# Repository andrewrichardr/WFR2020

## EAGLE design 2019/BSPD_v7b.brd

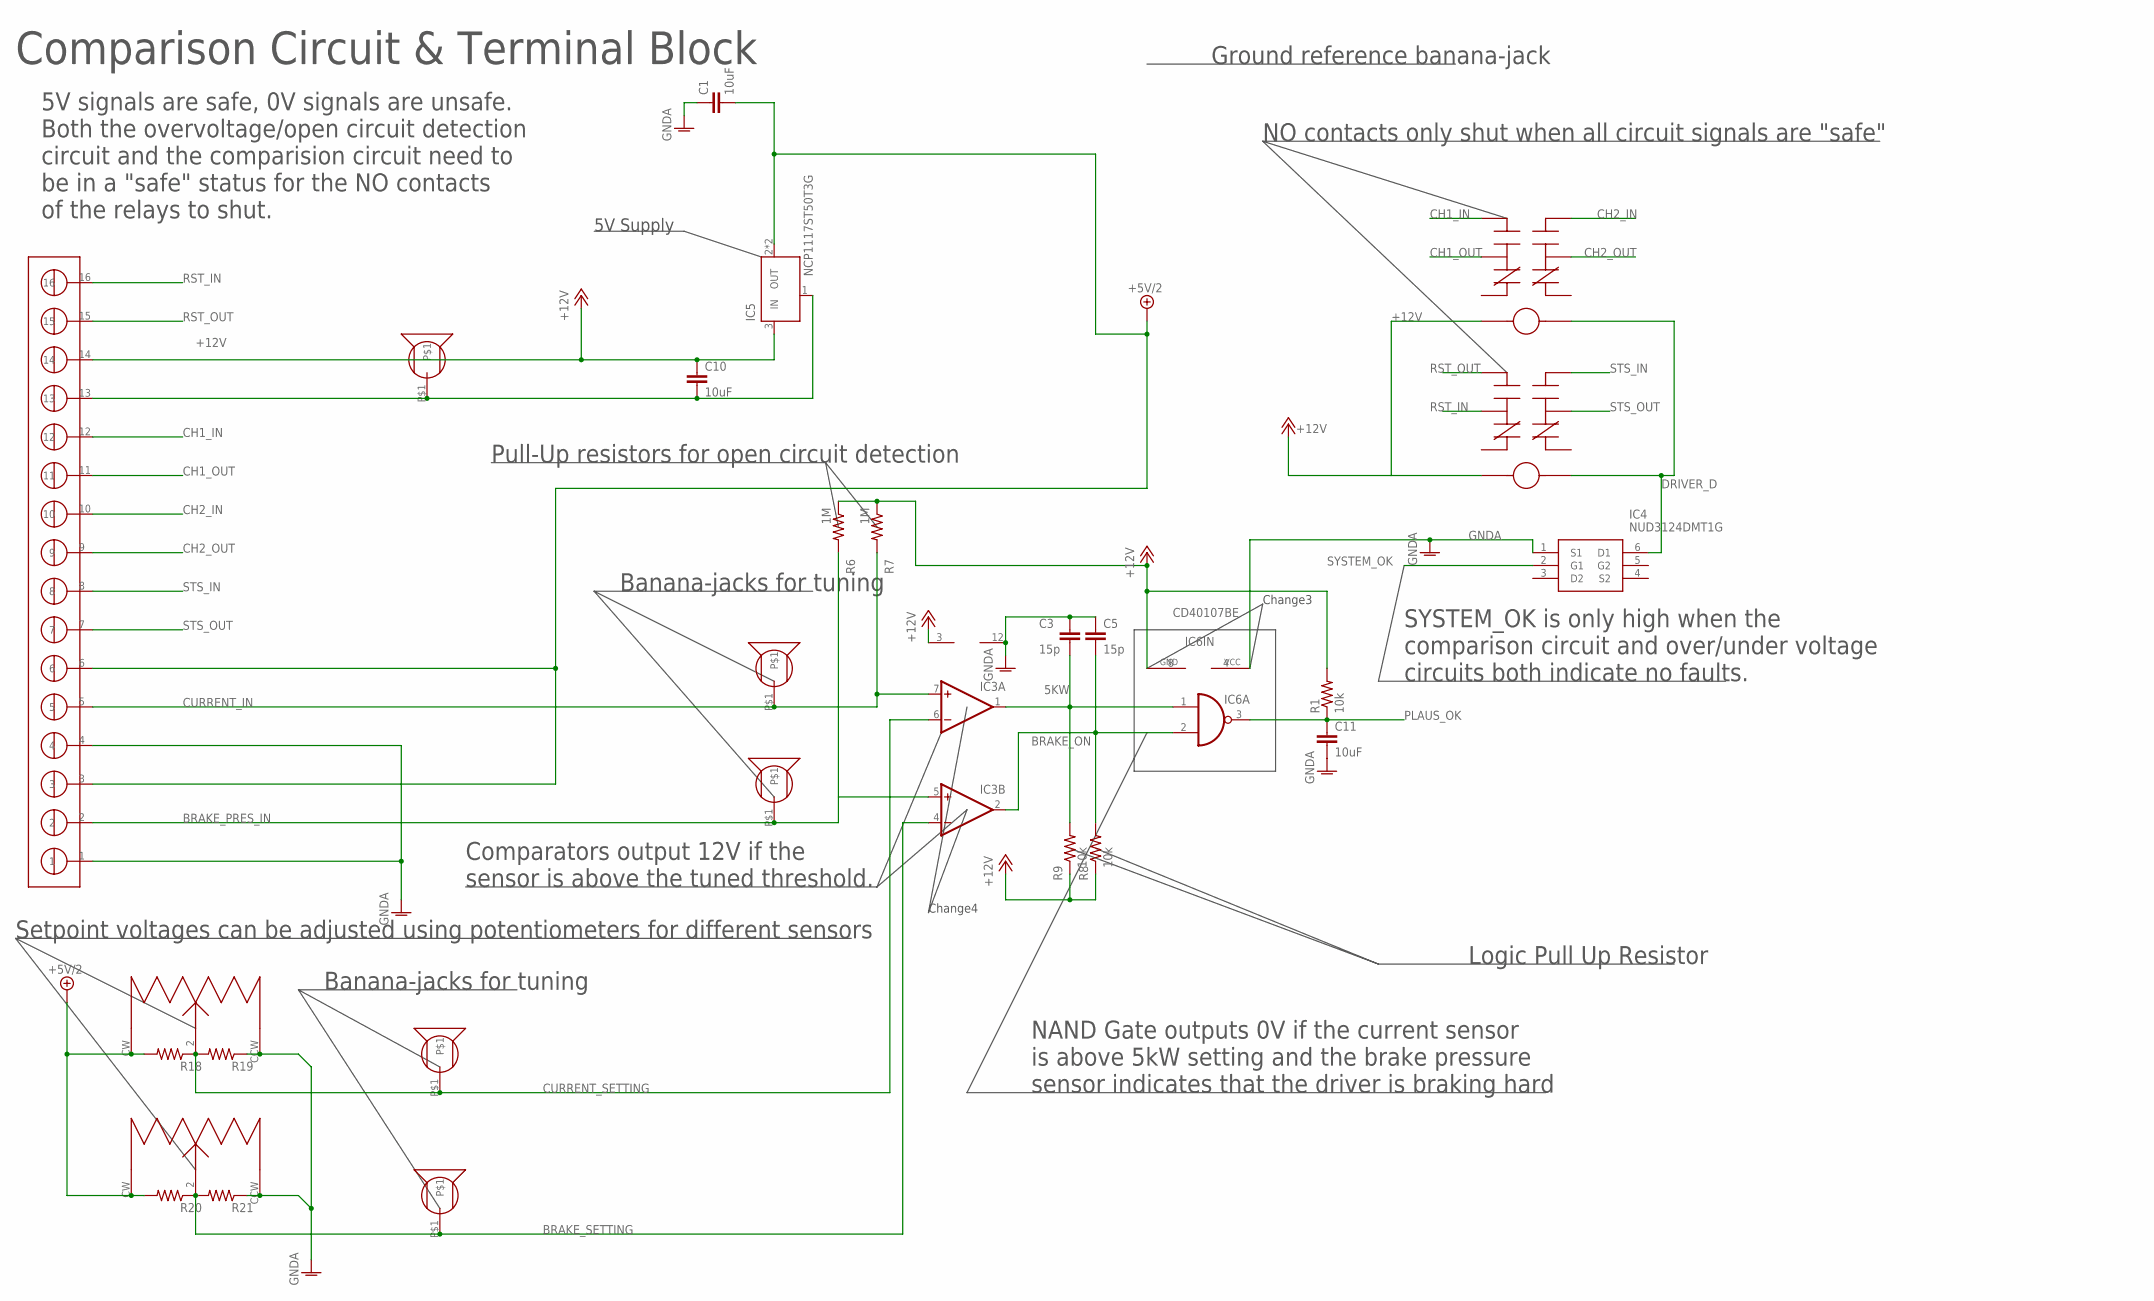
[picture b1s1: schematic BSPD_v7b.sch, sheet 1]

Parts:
C1, C10, C11: 10uF; C0805
C3, C5: 15p; C0805
IC3: 4AMP_P11+7N; DIL14
IC4: NUD3124DMT1G; SOT95P275X110-6N
IC5: NCP1117ST50T3G; SOT223
IC6: CD40107BE; DIL08
R1, R8, R9: 10k; M0805
R6, R7: 1M; M0805
R18, R19, R20, R21: R-US_M0805; M0805
U$1: BSPD_PARTS_AMPH_OQ1632500000G; BSPD_PARTS_3_81MM_16PIN
U$4, U$18, U$19, U$21, U$22: BSPD_PARTS_MP_BANANA_PLUG; BSPD_PARTS_BANANA_PLUG
U$10, U$11: POT_3310Y-025-103L; 3310Y
U$12, U$13: BSPD_PARTS_RLY_V23079A1001B301; BSPD_PARTS_V23079F1101B301

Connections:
5KW: C3.2, IC3.1 (OUT), IC6.1 (I0), R9.2
+5V/2: C1.2, IC5.2 (OUT), IC5.4 (OUT), R18.2, R20.2, U$1.3, U$1.6, U$10.CW, U$11.CW; also elsewhere on the board
+12V: C10.1, IC3.3 (V+), IC5.3 (IN), IC6.8 (GND), R1.2, R6.1, R7.1, R8.1, R9.1, U$1.14, U$12.1, U$13.1; also elsewhere on the board
BRAKE_ON: C5.2, IC3.2 (OUT), IC6.2 (I1), R8.2
BRAKE_PRES_IN: IC3.5 (+IN), R6.2, U$1.2, U$22.P$1; also elsewhere on the board
BRAKE_SETTING: IC3.4 (-IN), R20.1, R21.2, U$10.2 (VO), U$19.P$1
CH1_IN: U$1.12, U$13.5
CH1_OUT: U$1.11, U$13.4
CH2_IN: U$1.10, U$13.8
CH2_OUT: U$1.9, U$13.9
CURRENT_IN: IC3.7 (+IN), R7.2, U$1.5, U$21.P$1; also elsewhere on the board
CURRENT_SETTING: IC3.6 (-IN), R18.1, R19.2, U$11.2 (VO), U$18.P$1
DRIVER_D: IC4.6 (D1), U$12.12, U$13.12
GNDA: C1.1, C3.1, C5.1, C10.2, C11.2, IC3.12 (V-), IC4.1 (S1), IC5.1 (GND), IC6.4 (VCC), R19.1, R21.1, U$1.1, U$1.4, U$1.13, U$4.P$1, U$10.CCW, U$11.CCW; also elsewhere on the board
PLAUS_OK: C11.1, IC6.3 (O), R1.1; also elsewhere on the board
RST_IN: U$1.16, U$12.4
RST_OUT: U$1.15, U$12.5
STS_IN: U$1.8, U$12.8
STS_OUT: U$1.7, U$12.9
SYSTEM_OK: IC4.2 (G1); also elsewhere on the board

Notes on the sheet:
Comparison Circuit & Terminal Block
Logic Pull Up Resistor
Pull-Up resistors for open circuit detection
Banana-jacks for tuning
Setpoint voltages can be adjusted using potentiometers for different sensors
Ground reference banana-jack
5V Supply
NO contacts only shut when all circuit signals are "safe"
5V signals are safe, 0V signals are unsafe. Both the overvoltage/open circuit detection circuit and the comparision circuit need to be in a "safe" status for the NO contacts of the relays to shut.
NAND Gate outputs 0V if the current sensor is above 5kW setting and the brake pressure sensor indicates that the driver is braking hard
Comparators output 12V if the sensor is above the tuned threshold.
SYSTEM_OK is only high when the comparison circuit and over/under voltage circuits both indicate no faults.
Change3
Change4

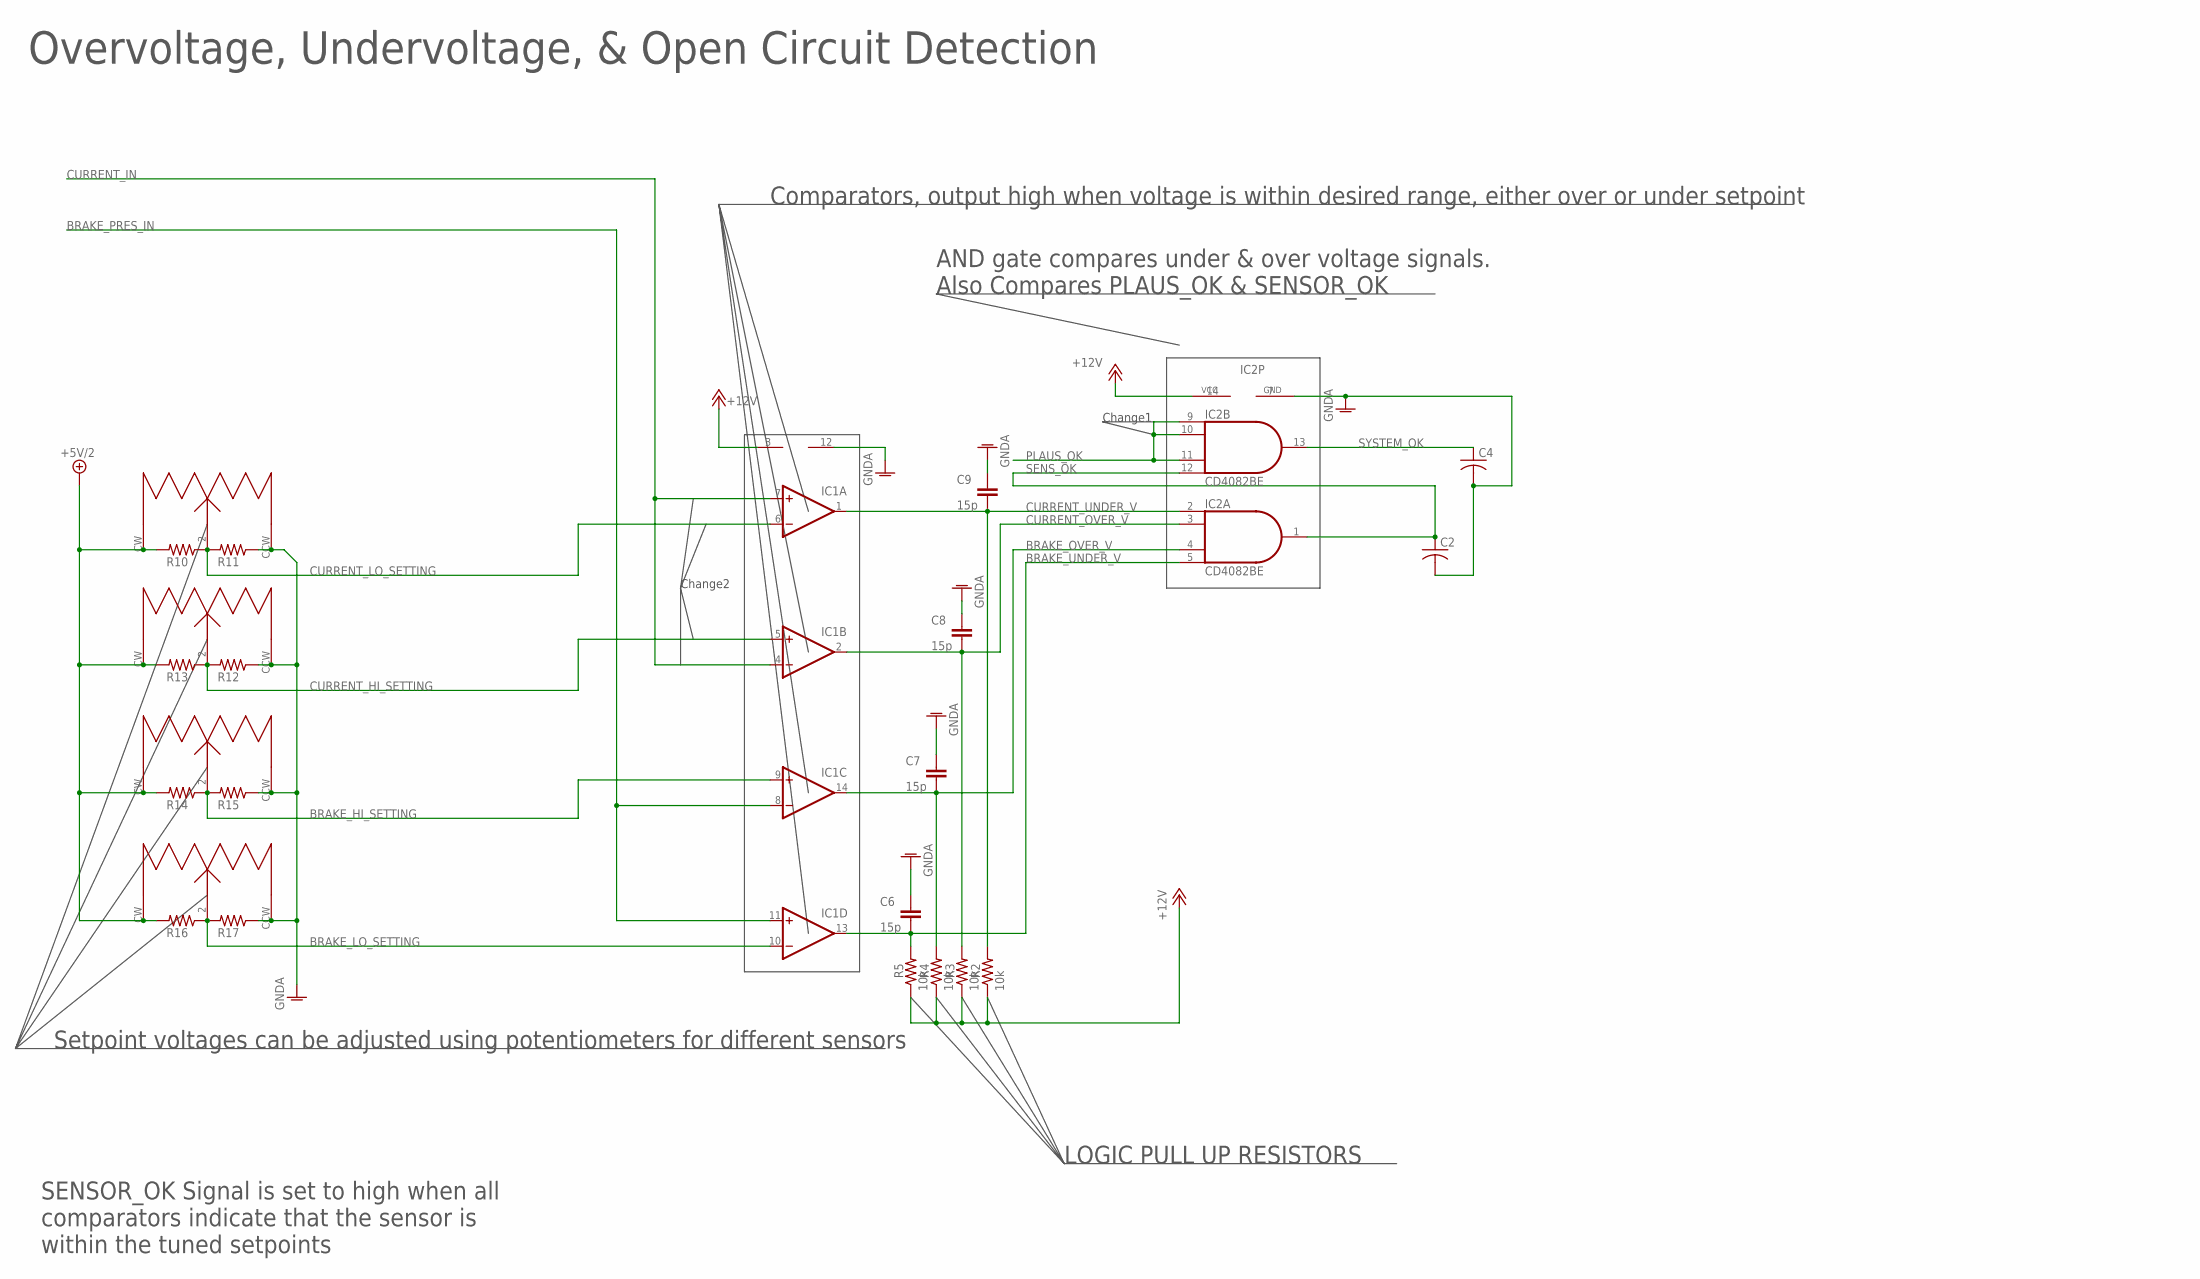
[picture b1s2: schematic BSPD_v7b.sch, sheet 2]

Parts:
C2, C4: C-USC0805; C0805
C6, C7, C8, C9: 15p; C0805
IC1: 4AMP_P11+7N; DIL14
IC2: CD4082BE; DIL14
R2, R3, R4, R5: 10k; M0805
R10, R11, R12, R13, R14, R15, R16, R17: R-US_M0805; M0805
U$6, U$7, U$8, U$9: POT_3310Y-025-103L; 3310Y

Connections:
+5V/2: R10.2, R13.2, R14.2, R16.2, U$6.CW, U$7.CW, U$8.CW, U$9.CW; also elsewhere on the board
+12V: IC1.3 (V+), IC2.14 (VCC), R2.1, R3.1, R4.1, R5.1; also elsewhere on the board
BRAKE_HI_SETTING: IC1.9 (+IN), R14.1, R15.2, U$8.2 (VO)
BRAKE_LO_SETTING: IC1.10 (-IN), R16.1, R17.2, U$9.2 (VO)
BRAKE_OVER_V: C7.2, IC1.14 (OUT), IC2.4 (I2), R4.2
BRAKE_PRES_IN: IC1.8 (-IN), IC1.11 (+IN); also elsewhere on the board
BRAKE_UNDER_V: C6.2, IC1.13 (OUT), IC2.5 (I3), R5.2
CURRENT_HI_SETTING: IC1.5 (+IN), R12.2, R13.1, U$7.2 (VO)
CURRENT_IN: IC1.4 (-IN), IC1.7 (+IN); also elsewhere on the board
CURRENT_LO_SETTING: IC1.6 (-IN), R10.1, R11.2, U$6.2 (VO)
CURRENT_OVER_V: C8.2, IC1.2 (OUT), IC2.3 (I1), R3.2
CURRENT_UNDER_V: C9.2, IC1.1 (OUT), IC2.2 (I0), R2.2
GNDA: C2.2, C4.2, C6.1, C7.1, C8.1, C9.1, IC1.12 (V-), IC2.7 (GND), R11.1, R12.1, R15.1, R17.1, U$6.CCW, U$7.CCW, U$8.CCW, U$9.CCW; also elsewhere on the board
PLAUS_OK: IC2.9 (I0), IC2.10 (I1), IC2.11 (I2); also elsewhere on the board
SENS_OK: C2.1, IC2.1 (O), IC2.12 (I3)
SYSTEM_OK: C4.1, IC2.13 (O); also elsewhere on the board

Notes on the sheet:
Overvoltage, Undervoltage, & Open Circuit Detection
Setpoint voltages can be adjusted using potentiometers for different sensors
AND gate compares under & over voltage signals. Also Compares PLAUS_OK & SENSOR_OK
Comparators, output high when voltage is within desired range, either over or under setpoint
SENSOR_OK Signal is set to high when all comparators indicate that the sensor is within the tuned setpoints
LOGIC PULL UP RESISTORS
Change1
Change2

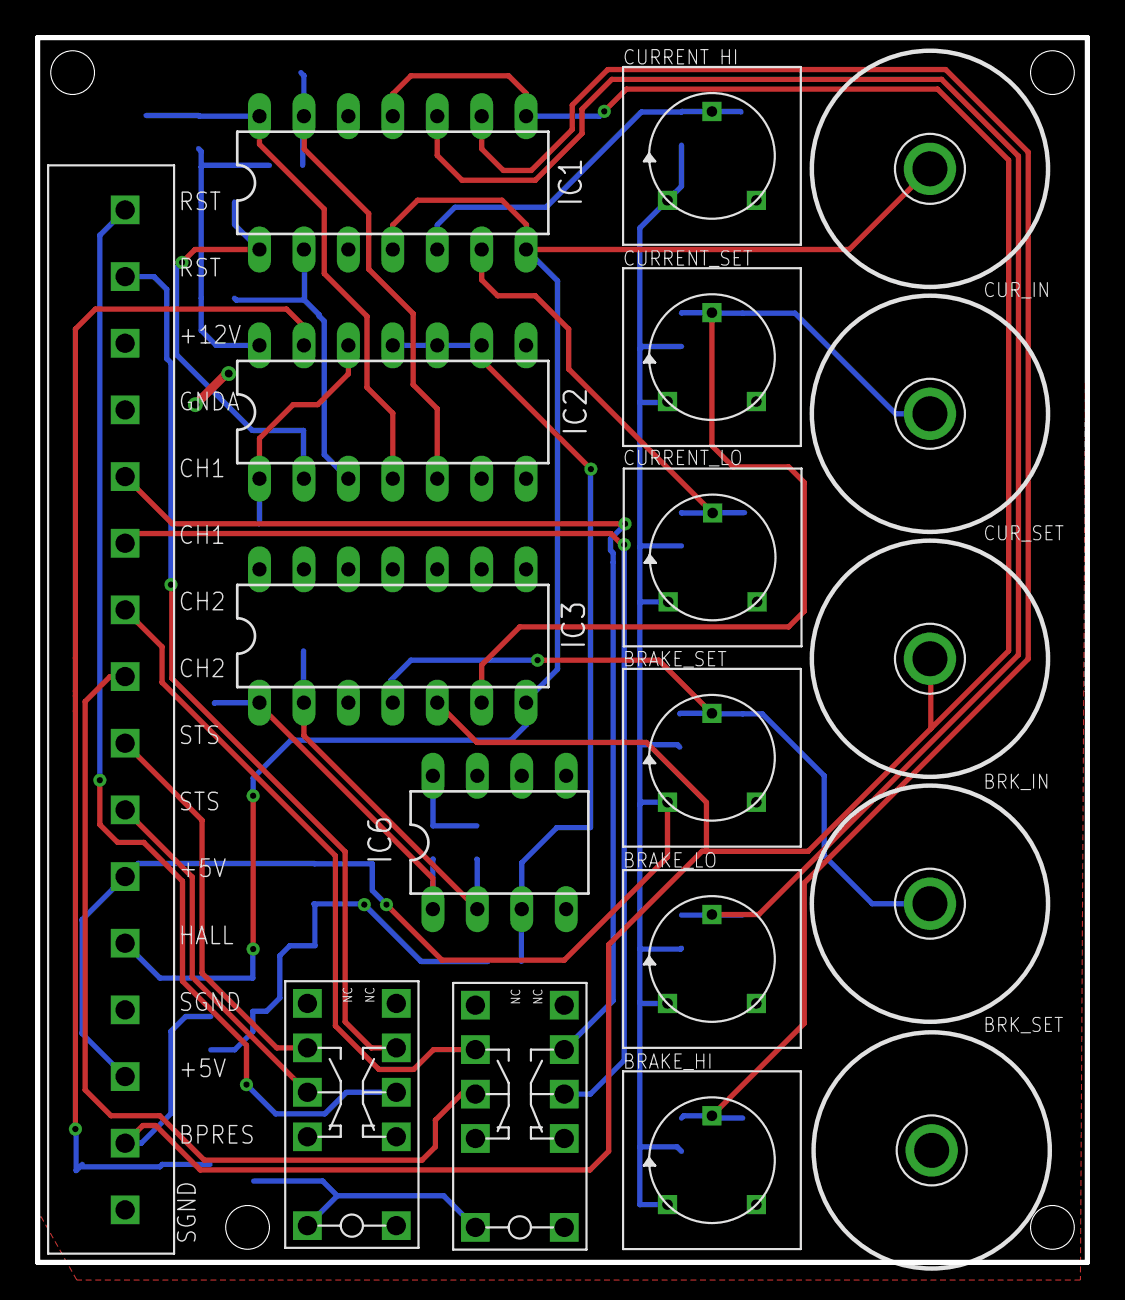
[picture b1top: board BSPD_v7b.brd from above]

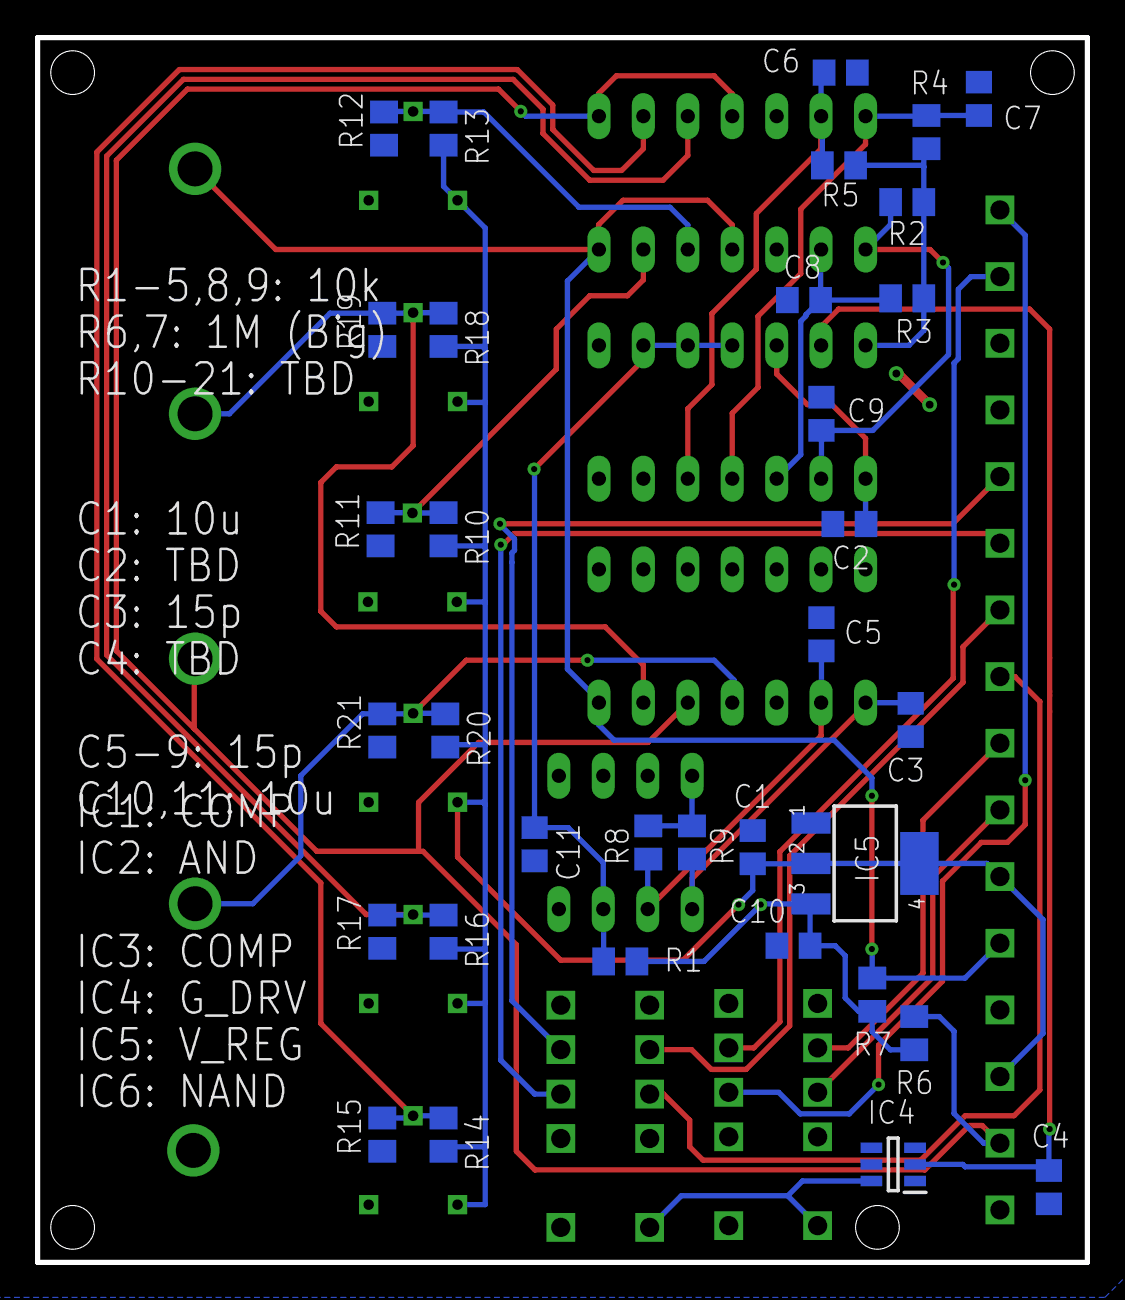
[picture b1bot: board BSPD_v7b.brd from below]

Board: 2 copper layers, 60.0 x 70.0 mm, 52 parts (34 on the bottom side), 29 nets.

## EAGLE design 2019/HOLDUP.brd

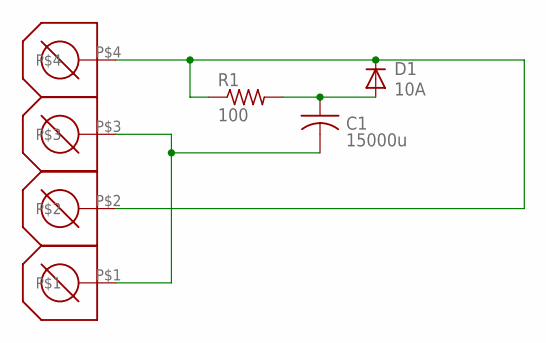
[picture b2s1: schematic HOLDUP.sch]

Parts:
C1: 15000u; CAPPRD750W65D1800H3700B
D1: 10A; DIOAD1570W120L850D500B
J1: TE_282834-4; 282834-4_FOOT
R1: 100; RESAD976W63L650D250B

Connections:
unnamed: D1.1 (C), J1.P$2, J1.P$4, R1.1
unnamed: C1.2, J1.P$1, J1.P$3
unnamed: C1.1, D1.2 (A), R1.2

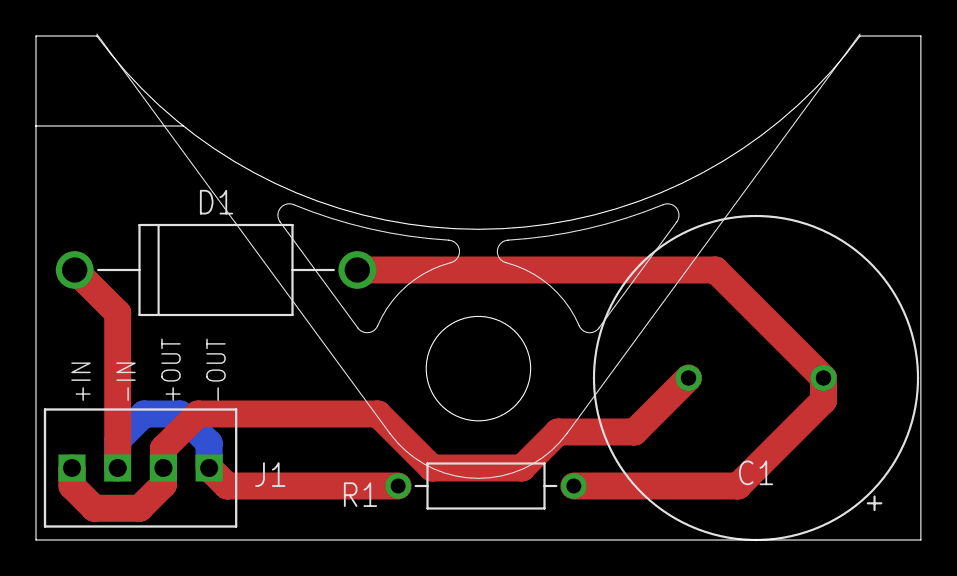
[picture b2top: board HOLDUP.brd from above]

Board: 2 copper layers, 49.2 x 28.0 mm, 4 parts (0 on the bottom side), 3 nets.

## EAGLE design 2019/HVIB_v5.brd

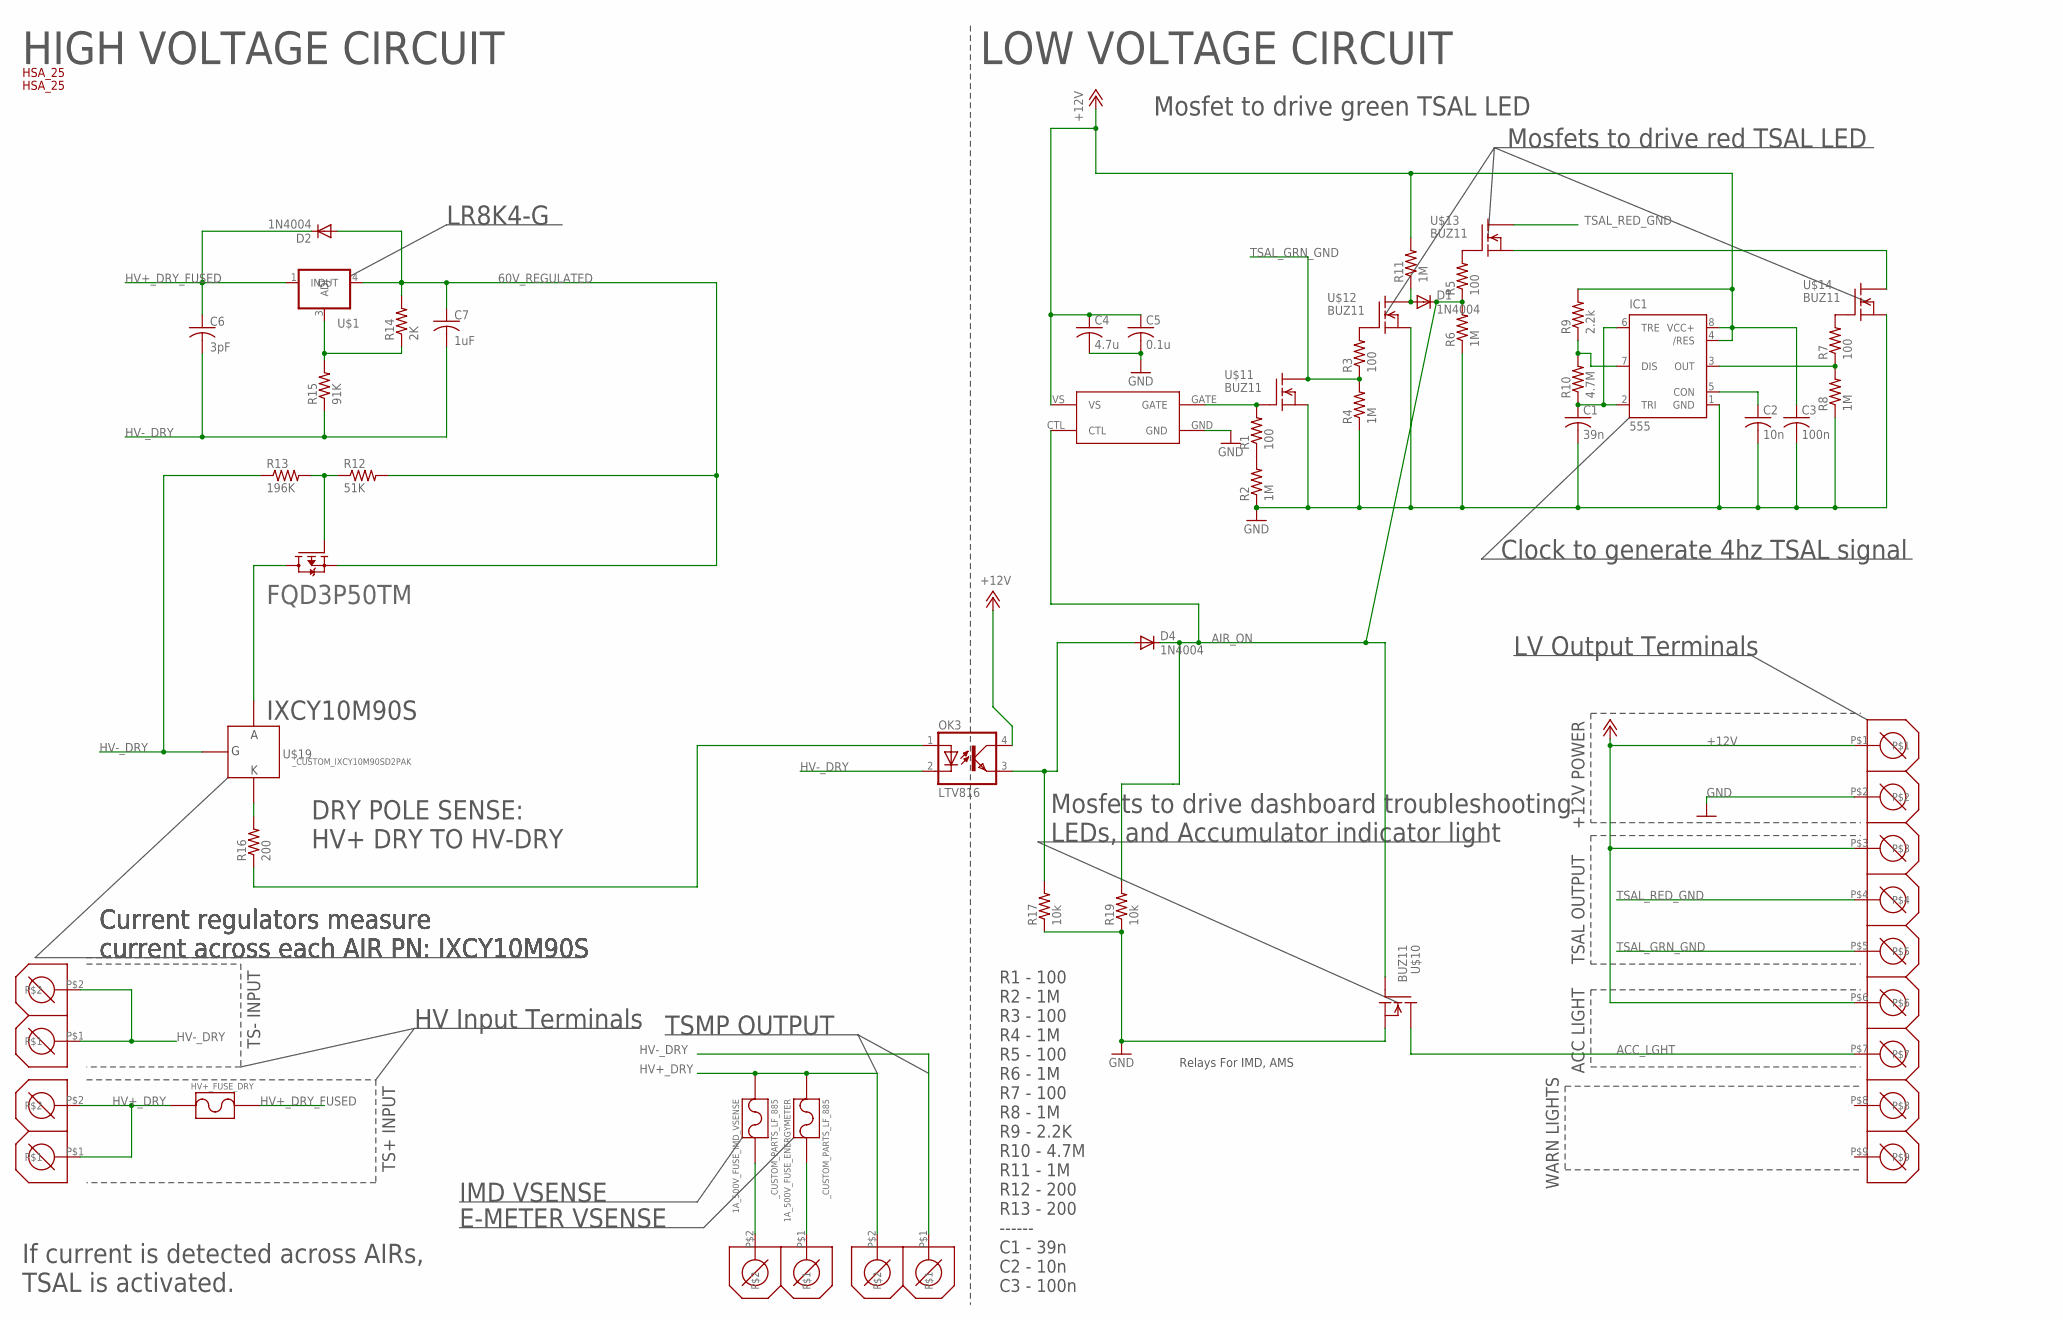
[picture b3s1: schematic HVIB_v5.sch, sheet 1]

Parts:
1A_500V_FUSE_ENERGYMETER, 1A_500V_FUSE_IMD_VSENSE: _CUSTOM_PARTS_LF_885
C1: 39n; C0805
C2: 10n; C0805
C3: 100n; C0805
C4: 4.7u; C0805
C5: 0.1u; C0805
C6: 3pF; 1111_2828METRIC
C7: 1uF; C2220K
D1, D2, D4: 1N4004; DO41-10
FQD3P50TM: FDD4141TO252; TO252
HV+_FUSE_DRY: _CUSTOM_PARTS_LF_885
IC1: 555; DIP08
OK3: LTV816; DIL04
R1, R3, R5, R7: 100; R0805
R2, R4, R6, R8, R11: 1M; R0805
R9: 2.2k; R0805
R10: 4.7M; R0805
R12: 51K; R2010
R13: 196K; R2010
R14: 2K; R2010
R15: 91K; R2010
R16: 200; R2010
R17, R19: 10k; R0805
U$1: K4
U$2, U$3: HSA25; HSA_25_FOOT
U$4, U$6, U$16, U$17: DCDC_PARTS_282838-2_TE; DCDC_PARTS_282838-2_FOOT
U$7: PHOENIX_1725724; 1725724_FOOT
U$10, U$11, U$12, U$13, U$14: BUZ11; TO220
U$15: MIC4417; PDM_2019_REVB_MIC4416YM4-TR
U$19: _CUSTOM_IXCY10M90SD2PAK; TO228P991X238-3

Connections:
60V_REGULATED: C7.1, D2.A, FQD3P50TM.2 (S), R12.2, R14.2, U$1.4 (OUT)
+12V: C3.1, C4.1, C5.1, IC1.4 (/RES), IC1.8 (VCC+), OK3.4 (COL), R9.2, R11.2, U$7.P$1, U$7.P$3, U$7.P$6, U$15.VS
ACC_LGHT: U$7.P$7, U$10.2 (D)
AIR_ON: D1.C, D4.C, R5.1, R6.2, R19.2, U$10.1 (G), U$15.CTL
GND: C1.2, C2.2, C3.2, C4.2, C5.2, IC1.1 (GND), R2.1, R4.1, R6.1, R8.1, R17.1, R19.1, U$7.P$2, U$10.3 (S), U$11.3 (S), U$12.3 (S), U$14.3 (S), U$15.GND
HV+_DRY: 1A_500V_FUSE_ENERGYMETER.P$1, 1A_500V_FUSE_IMD_VSENSE.P$1, HV+_FUSE_DRY.P$2, U$6.P$1, U$6.P$2, U$16.P$2
HV+_DRY_FUSED: C6.P$1 (1), D2.C, HV+_FUSE_DRY.P$1, U$1.1 (IN)
HV-_DRY: C6.P$2 (2), C7.2, OK3.2 (C), R13.1, R15.1, U$4.P$1, U$4.P$2, U$16.P$1, U$19.1 (G)
unnamed: R1.1, R2.2
unnamed: R1.2, U$11.1 (G), U$15.GATE
unnamed: R3.2, U$12.1 (G)
unnamed: C2.1, IC1.5 (CON)
unnamed: IC1.7 (DIS), R9.1, R10.2
unnamed: R5.2, U$13.1 (G)
unnamed: R7.2, U$14.1 (G)
unnamed: IC1.3 (OUT), R7.1, R8.2
unnamed: C1.1, IC1.2 (TRI), IC1.6 (TRE), R10.1
unnamed: FQD3P50TM.3 (D), U$19.3 (A)
unnamed: FQD3P50TM.1 (G), R12.1, R13.2
unnamed: U$13.3 (S), U$14.2 (D)
unnamed: D4.A, OK3.3 (EMIT), R17.2
unnamed: D1.A, R11.1, U$12.2 (D)
unnamed: R16.2, U$19.2 (K)
unnamed: R14.1, R15.2, U$1.3 (ADJ)
unnamed: 1A_500V_FUSE_IMD_VSENSE.P$2, U$17.P$2
unnamed: 1A_500V_FUSE_ENERGYMETER.P$2, U$17.P$1
unnamed: OK3.1 (A), R16.1
TSAL_GRN_GND: R3.1, R4.2, U$7.P$5, U$11.2 (D)
TSAL_RED_GND: U$7.P$4, U$13.2 (D)

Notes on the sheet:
HIGH VOLTAGE CIRCUIT
LOW VOLTAGE CIRCUIT
TSAL OUTPUT
ACC LIGHT
WARN LIGHTS
Current regulators measure current across each AIR PN: IXCY10M90S
Mosfets to drive dashboard troubleshooting LEDs, and Accumulator indicator light
Clock to generate 4hz TSAL signal
Mosfets to drive red TSAL LED
Mosfet to drive green TSAL LED
+12V POWER
TS- INPUT
TS+ INPUT
If current is detected across AIRs, TSAL is activated.
HV Input Terminals
LV Output Terminals
R1 - 100 R2 - 1M R3 - 100 R4 - 1M R5 - 100 R6 - 1M R7 - 100 R8 - 1M R9 - 2.2K R10 - 4.7M R11 - 1M R12 - 200 R13 - 200 ------ C1 - 39n C2 - 10n C3 - 100n
TSMP OUTPUT
E-METER VSENSE
IMD VSENSE
DRY POLE SENSE: HV+ DRY TO HV-DRY
Relays For IMD, AMS
IXCY10M90S
LR8K4-G

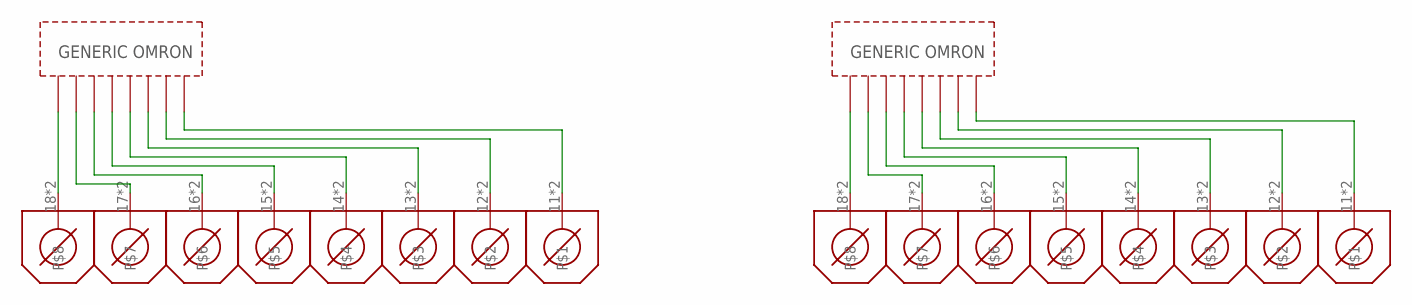
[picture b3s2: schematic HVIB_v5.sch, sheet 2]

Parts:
U$5, U$8: G2R_RLY; OMRON_RLY_FOOT
U$9, U$18: PHOENIX_1771017; 8PIN_HEAD

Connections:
unnamed: U$5.1, U$9.18, U$9.28
unnamed: U$5.2, U$9.17, U$9.27
unnamed: U$5.3, U$9.16, U$9.26
unnamed: U$5.4, U$9.15, U$9.25
unnamed: U$5.5, U$9.14, U$9.24
unnamed: U$5.6, U$9.13, U$9.23
unnamed: U$5.7, U$9.12, U$9.22
unnamed: U$5.8, U$9.11, U$9.21
unnamed: U$8.1, U$18.18, U$18.28
unnamed: U$8.2, U$18.17, U$18.27
unnamed: U$8.3, U$18.16, U$18.26
unnamed: U$8.4, U$18.15, U$18.25
unnamed: U$8.5, U$18.14, U$18.24
unnamed: U$8.6, U$18.13, U$18.23
unnamed: U$8.7, U$18.12, U$18.22
unnamed: U$8.8, U$18.11, U$18.21

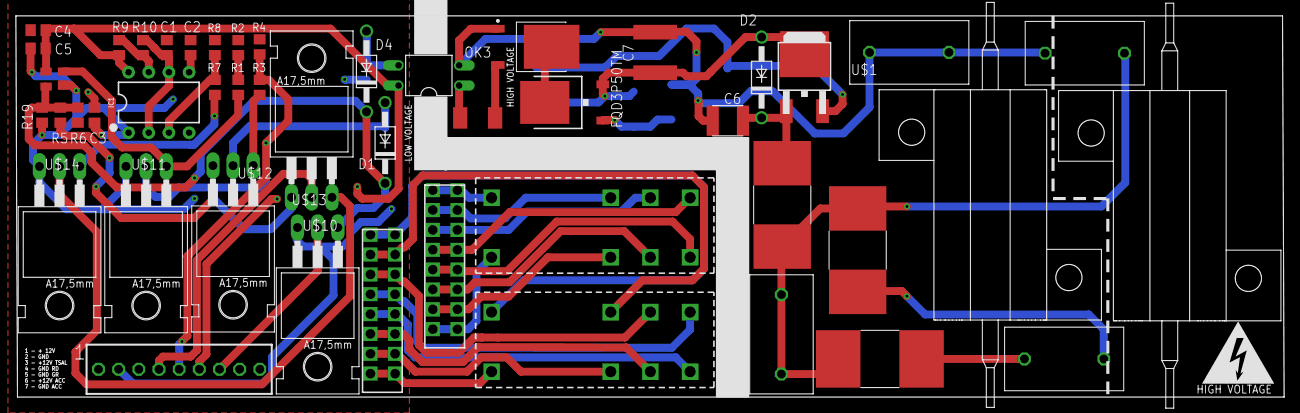
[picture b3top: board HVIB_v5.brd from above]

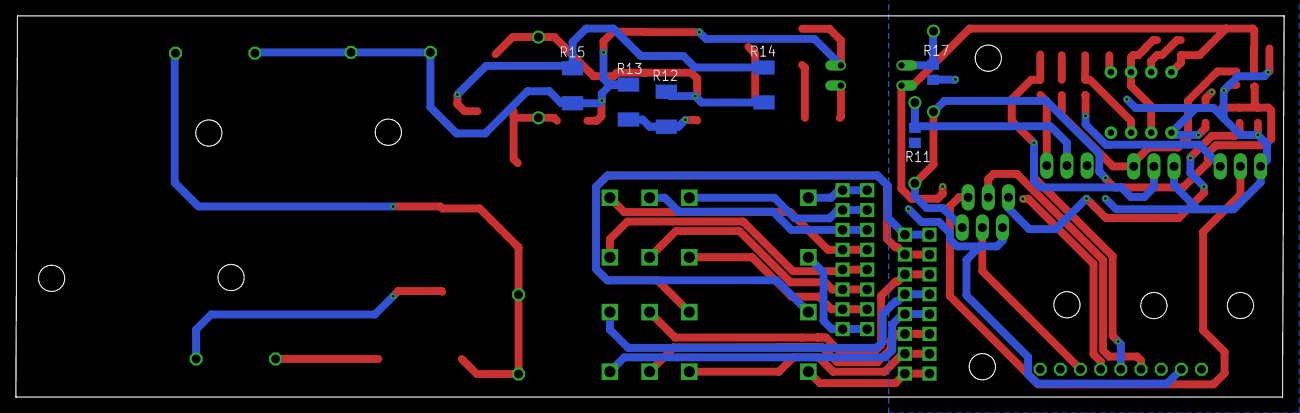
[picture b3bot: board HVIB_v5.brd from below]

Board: 2 copper layers, 159.7 x 48.0 mm, 53 parts (6 on the bottom side), 45 nets.

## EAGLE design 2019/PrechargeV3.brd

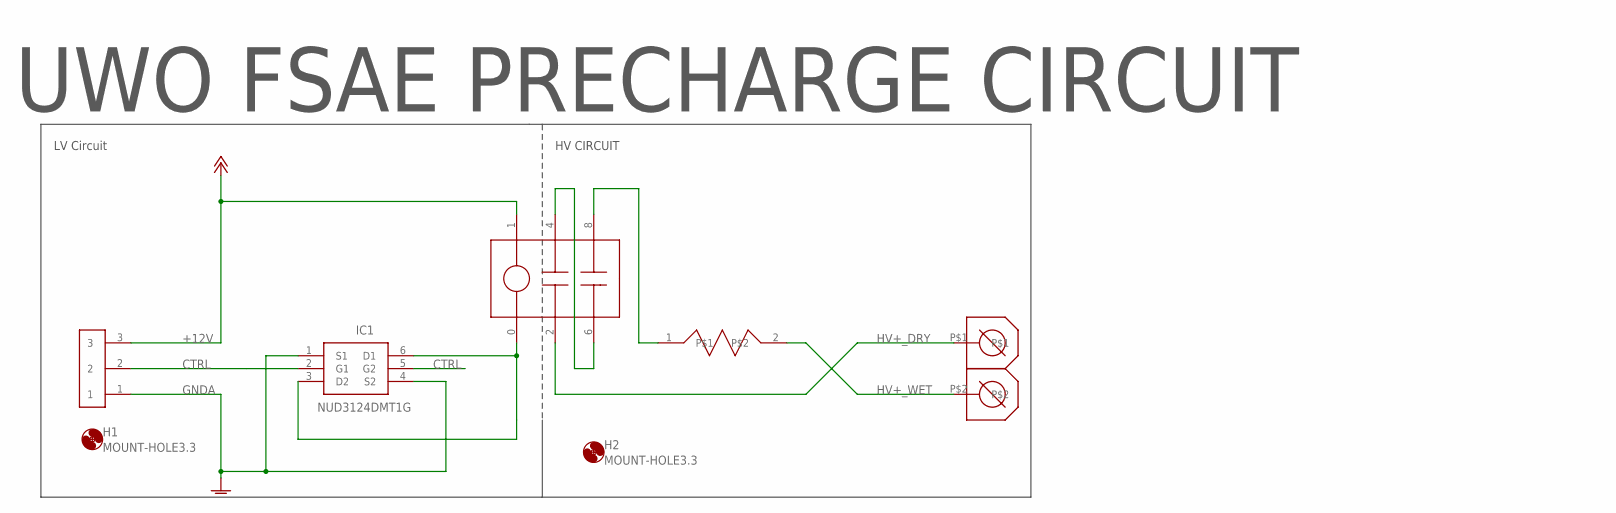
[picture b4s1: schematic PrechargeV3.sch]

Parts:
H1, H2: MOUNT-HOLE3.3; 3,3
IC1: NUD3124DMT1G; SAMACSYS_PARTS_SOT95P275X110-6N
U$1: TO247RESISTORHEATINK; _CUSTOM_TO-247-2V
U$2: PHOENIX_1935789
U$3: G7L
U$17: 282838-2_TE; 282838-2_FOOT

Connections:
+12V: U$2.3, U$3.1
CTRL: IC1.2 (G1), IC1.5 (G2), U$2.2
GNDA: IC1.1 (S1), IC1.4 (S2), U$2.1
HV+_DRY: U$3.2, U$17.P$1
HV+_WET: U$1.2, U$17.P$2
unnamed: U$1.1, U$3.8
unnamed: U$3.4, U$3.6
unnamed: IC1.3 (D2), IC1.6 (D1), U$3.0

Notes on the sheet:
UWO FSAE PRECHARGE CIRCUIT
LV Circuit
HV CIRCUIT

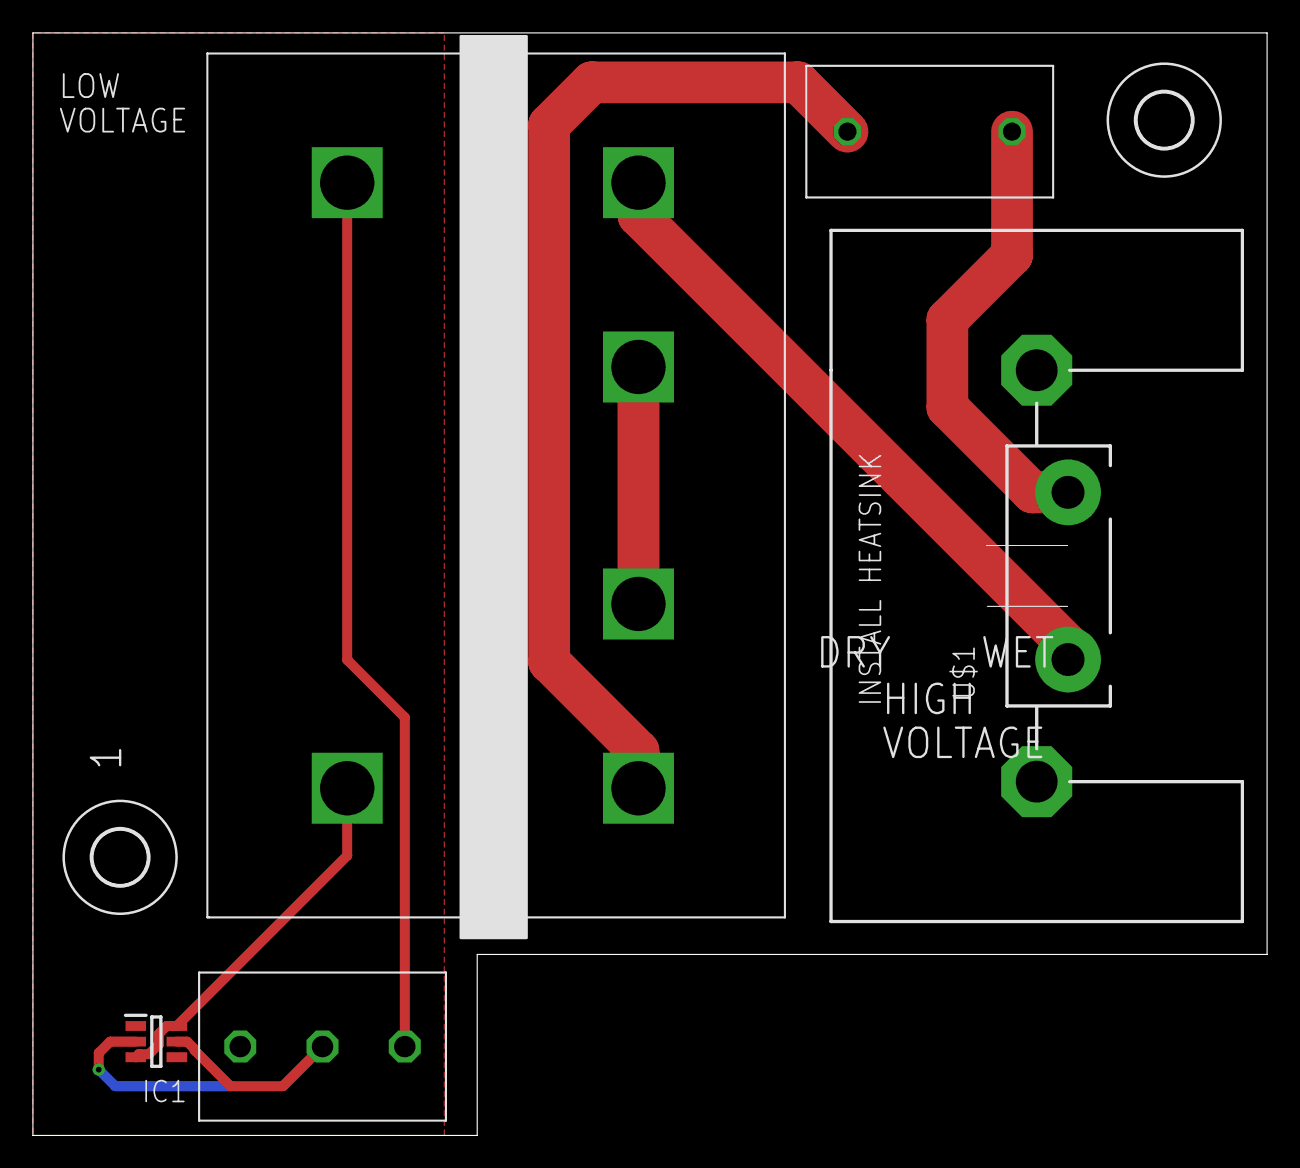
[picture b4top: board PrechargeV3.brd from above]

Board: 2 copper layers, 75.0 x 67.0 mm, 7 parts (0 on the bottom side), 8 nets.

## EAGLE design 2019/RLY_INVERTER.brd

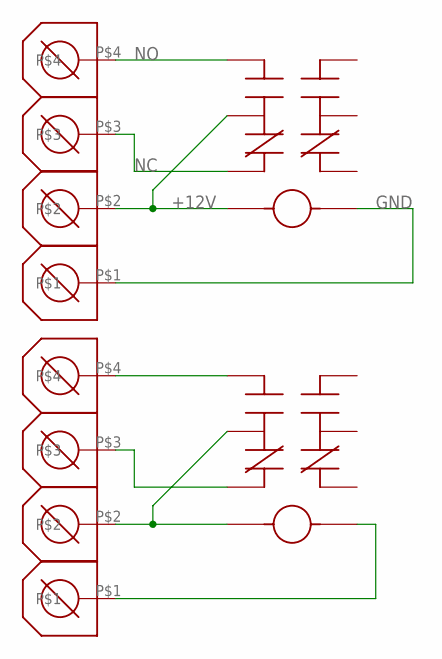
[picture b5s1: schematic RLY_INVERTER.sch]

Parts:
J1, J2: TE_282834-4; 282834-4_FOOT
U$1, U$2: BSPD_PARTS_RLY_V23079A1001B301; BSPD_PARTS_V23079F1101B301

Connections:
+12V: J2.P$2, U$2.1, U$2.4
GND: J2.P$1, U$2.12
unnamed: J1.P$1, U$1.12
unnamed: J1.P$2, U$1.1, U$1.4
unnamed: J1.P$4, U$1.5
unnamed: J1.P$3, U$1.3
NC: J2.P$3, U$2.3
NO: J2.P$4, U$2.5

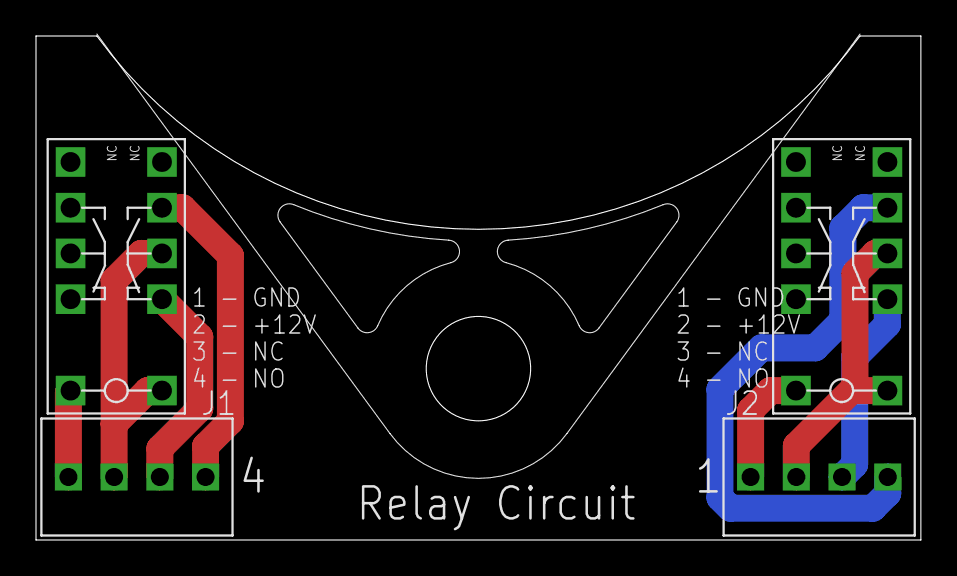
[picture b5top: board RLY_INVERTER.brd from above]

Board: 2 copper layers, 49.2 x 28.0 mm, 4 parts (0 on the bottom side), 8 nets.

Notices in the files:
parts and their libraries:
SparkFun-IC-Special-Function: Licensing: Creative Commons ShareAlike 4.0 International - https://creativecommons.org/licenses/by-sa/4.0
